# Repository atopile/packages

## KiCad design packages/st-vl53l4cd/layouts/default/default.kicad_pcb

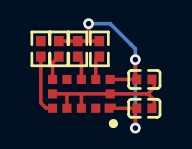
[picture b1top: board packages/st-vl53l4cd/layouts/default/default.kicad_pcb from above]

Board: 2 copper layers, 7 parts (0 on the bottom side), 6 nets.

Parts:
C1: 1F; C0402
C2: 4.7e-F; C0402
R1, R2: 4700Ω; R0402
R3, R4: 10000Ω; R0402
U1: LGA-12_L4.4-W2.4_VL53L0X

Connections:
7: R3.2, U1.7
SCL: R1.1, U1.10
SDA: R2.1, U1.9
XSHUT: R4.2, U1.5
hv: C1.1, C2.1, R1.2, R2.2, R3.1, R4.1, U1.1, U1.11
lv: C1.2, C2.2, U1.3, U1.4, U1.6, U1.12

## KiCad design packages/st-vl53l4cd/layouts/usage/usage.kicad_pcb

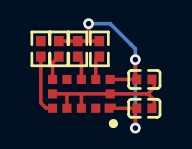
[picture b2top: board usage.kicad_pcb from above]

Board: 2 copper layers, 7 parts (0 on the bottom side), 6 nets.

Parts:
C1: 1F; C0402
C2: 4.7e-F; C0402
R1, R2: 10000Ω; R0402
R3, R4: 4700Ω; R0402
U1: LGA-12_L4.4-W2.4_VL53L0X

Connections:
7: R1.2, U1.7
SCL: R3.1, U1.10
SDA: R4.1, U1.9
XSHUT: R2.2, U1.5
hv: C1.1, C2.1, R1.1, R2.1, R3.2, R4.2, U1.1, U1.11
lv: C1.2, C2.2, U1.3, U1.4, U1.6, U1.12

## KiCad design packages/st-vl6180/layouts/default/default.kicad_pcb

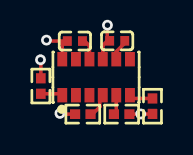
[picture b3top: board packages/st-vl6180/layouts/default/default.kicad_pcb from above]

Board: 2 copper layers, 7 parts (0 on the bottom side), 7 nets.

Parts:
C1, C2: 1F; C0402
R1, R2: 47000Ω; R0402
R3, R4: 10000Ω; R0402
U1: LGA-12_L4.8-W2.8-P0.75-BL

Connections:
1: R2.1, U1.1
GPIO0_CE: R1.1, U1.4
SCL: R3.1, U1.5
SDA: R4.1, U1.6
hv: C1.1, R1.2, R2.2, R3.2, R4.2, U1.10
lv: C1.2, C2.2, U1.9, U1.12
power_vcsel_cap-power-hv: C2.1, U1.8

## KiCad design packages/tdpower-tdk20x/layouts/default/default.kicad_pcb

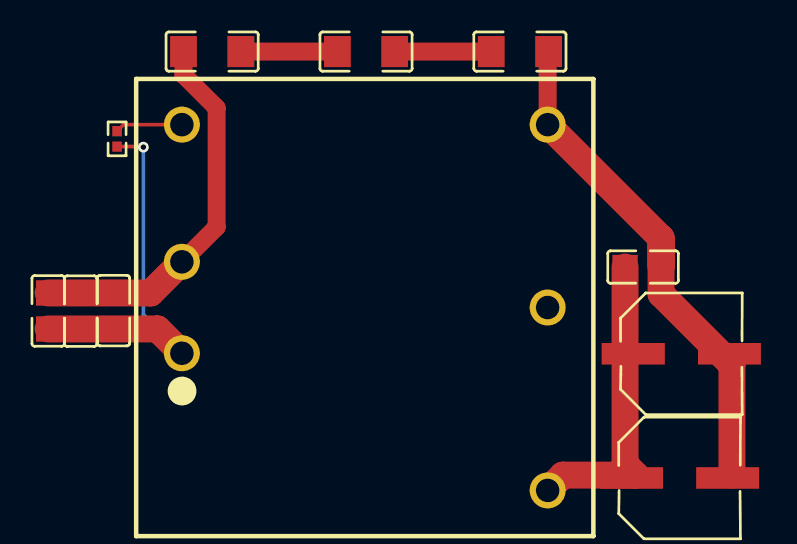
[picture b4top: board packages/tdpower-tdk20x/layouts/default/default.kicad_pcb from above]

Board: 2 copper layers, 11 parts (0 on the bottom side), 7 nets.

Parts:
C1, C2, C3, C4: [capacitance: unknown]; C0805
C5, C6: CAP-SMD_BD6.3-L6.6-W6.6-FD
C7, C8, C9: [capacitance: unknown]; C1206
R1: [resistance: unknown]; R0402
U1: PWRM-TH_TDPOWER_TDK20-XXSXXWH

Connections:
CNT: R1.1, U1.3
hv: C1.1, C2.1, C3.1, R1.2, U1.1
lv: C4.2, C5.2, C6.2, C9.2, U1.4
output_cap_1-power-hv: C4.1, C5.1, C6.1, U1.6
y_caps[0]-power-hv: C1.2, C2.2, C3.2, C7.1, U1.2
y_caps[1]-power-hv: C7.2, C8.1
y_caps[2]-power-hv: C8.2, C9.1
